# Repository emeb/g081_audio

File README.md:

# g081_audio

A Eurorack reverb module based on the STM32G081

## What it is

The G081 Audio module is an extremely simplified audio effects processor for Eurorack that's designed specifically to run the original MIDIVerb algorithms. Its audio conversion resolution is comparable to the original MIDIVerb and its processing power and memory capacity are just enough to handle the requirements of the algorithms. Essentially it is a proof-of-concept in minimalism.

## Background

In 2021 I was involved in a project to reverse-engineer the MIDIVerb which I've documented over here: [MIDIVerb_RE](https://github.com/emeb/MIDIVerb_RE). Once that effort was wrapped up I had some curiosity about how well those algorithms could be implemented on modern low-cost microprocessors so I did some tests that showed the initial emulation approach was too costly to run well on low-spec processors because there was considerable overhead in the the interpretation approach that was used. The alternative was to "compile" the algorithms into equivalent C code which could then be further optimized into fast machine code by high quality C compilers available today. This is the method used in the G081 Audio module.

## Hardware Features

The hardware of the module includes the following features:

- STM32G081KB Arm Cortex M0+ microcontroller
  - 64MHz
  - 128kB Flash
  - 36kB SRAM
  - 12-bit ADC with multipexed inputs
  - 2x 12-bit DACs
  - I2S, I2C and SPI ports
- PT8211 I2S stereo DAC
  - choice of on-chip DAC or I2S DAC for Euro-level audio outputs 
- Optional SPI flash chip (up to 32MB capacity)
- 12MHz crystal oscillator
- 64x32 I2C OLED display
- 2 CV inputs (+/-5V range with offset pots)
- Stereo audio inputs (12-bit resolution, +/-7V range)
- Stereo audio outputs (12- or 16-bit resolution, +/-7V range)
- 3.3V logic-level full-duplex serial port for diagnostics
- 6HP wide
- Standard 16-pin Euro power jack w/ shroud and reverse protection.

The main board has components on both sides - pots, jacks and OLED display on the front and all the remaining parts, including the Eurorack power jack on the back. The board has two "solder blob" type jumpers which allow selection of the output source - either the DACs internal to the STM32G081 or the PT8211 I2S DAC - the present firmware assumes the PT8211 is used. A footprint for an optional SPI flash chip is available although the present firmware does not require it.

## Firmware Features

The primary MIDIVerb software provides these features:

- 63 Original MIDIVerb algorithms selected by CV1
  - Smooth muting during program changes.
  - MIDIVerb algorithm number displayed on OLED.
  - Characteristics (duration, type) temporarily shown on display during changes.
- Wet/Dry mixing via CV2
  - Mix setting displayed on OLED.
- Input / Ouput level indicators
  - Low / normal / Clip level displayed as grayscale
- Compile-time option for OLED blanking.

## Design Collateral

This repository contains both Hardware and Firmware design info. Please refer to the README.md files withing the respective directories for further details.

[Hardware](./Hardware/README.md)

[Firmware](./Firmware/README.md)

## Build Notes

Since this project was first released there has been at least one alternate layout built by others in the community which unfortunately suffered from severe noise caused by the OLED which leaked into the audio path. The original layout provided here does not suffer from that problem so it's worthwhile noting that if you do choose to respin this design it would be wise to observe good layout principles:
- Maintain as contiguous a ground plane as is possible
- Think about the paths that supply and return currents are forced to take through your layout and how to keep the digital and analog paths separate.

In particular, the OLED is prone to generating strong current spikes when it is refreshing any active pixels and the PT8211 I2S DAC has very poor power supply rejection so when those two devices are present in the same design you must use care to keep them from fighting. I've provided a compile-time option to blank the OLED after a few seconds which can work around this issue but with good layout this should not be necessary.

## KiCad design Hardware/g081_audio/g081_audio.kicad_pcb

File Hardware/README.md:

# G081 Audio Hardware

This directory contains the KiCAD design files for the G081 Audio module, including both the passive front panel and the electrical rear panel.

A PDF schematic is available here: [G081 Audio Schematic](./g081_audio_schematic.pdf)

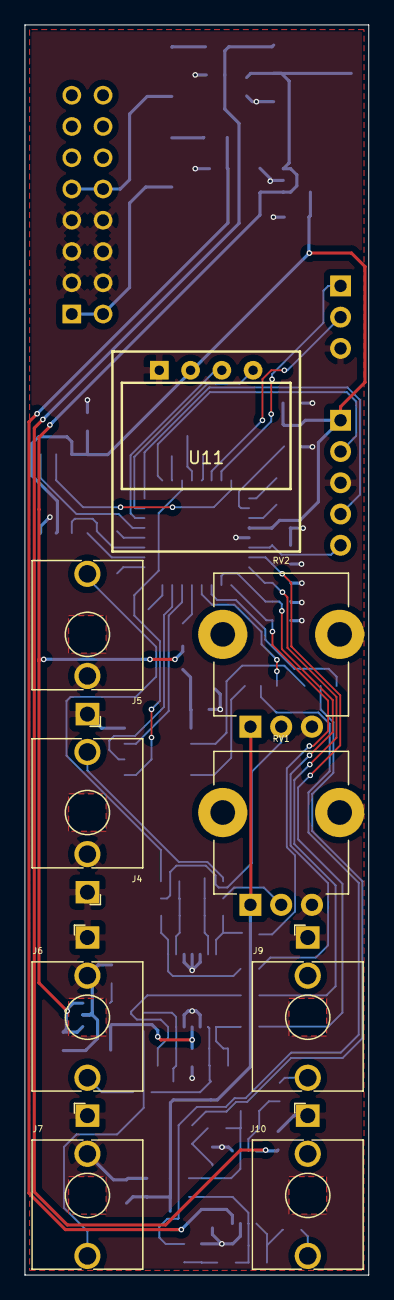
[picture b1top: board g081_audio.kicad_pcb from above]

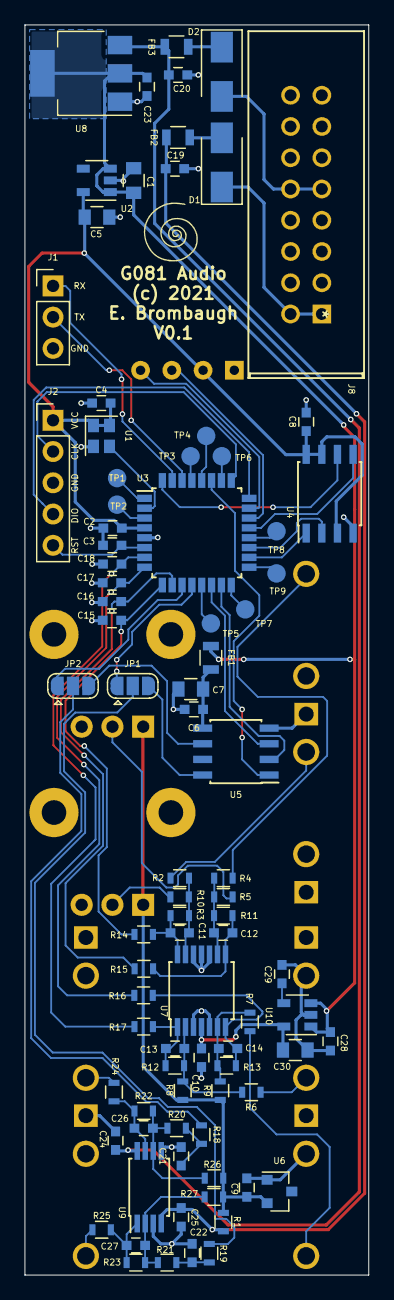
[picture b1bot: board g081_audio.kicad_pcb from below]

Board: 2 copper layers, 27.9 x 101.6 mm, 96 parts (87 on the bottom side), 69 nets.

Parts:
C1, C5, C7, C30: 10uf; C_0805
C2, C3, C4, C6, C8, C9, C10, C24, C25: 0.1uf; C_0603
C11, C12, C13, C14: 330pf; C_0603
C15, C16, C17, C18, C29: 0.01uf; C_0603
C19, C20, C23, C28: 1uf; C_0603
C21, C22: 4.7nf; C_0603
C26, C27: 75pf; C_0603
D1, D2: D; D_SMA
FB1, FB2, FB3: 220; R_0805
J1: Serial; Pin_Header_Straight_1x03_Pitch2.54mm
J2: SWD; Pin_Header_Straight_1x05_Pitch2.54mm
J4, J5, J6, J7, J9, J10: AudioJack2_SwitchT; Jack_3.5mm_QingPu_WQP-PJ398SM_Vertical_CircularHoles
J8: Conn_02x08_Odd_Even; 5103308-3
JP1, JP2: SolderJumper_3_Open; SolderJumper-3_P1.3mm_Open_RoundedPad1.0x1.5mm
R1: 1.5k; R_0603
R2, R4, R6, R7, R8, R9: 100k; R_0603
R3, R5: 49.9k; R_0603
R10, R11, R12, R13: 33k; R_0603
R14, R15, R16, R17, R24, R25: 100; R_0603
R18, R19: 1k; R_0603
R20, R21: 16k; R_0603
R22, R23, R26, R27: 71.5k; R_0603
RV1, RV2: 10k; Potentiometer_TT_P0915N
Ref**: Val**; avatar_small
TP1, TP2, TP3, TP4, TP5, TP6, TP7, TP8, TP9: TestPoint; Measurement_Point_Round-SMD-Pad_Small
U1: 12MHz; Oscillator_SMD_SeikoEpson_SG210-4pin_2.5x2.0mm
U2: MCP1802x-xx02xOT; SOT-23-5
U3: STM32G081KB; LQFP-32_7x7mm_Pitch0.8mm
U4: W25Q32JVSS; SOIC-8_208mil_Pitch1.27mm
U5: PT8211; SOIC-8_3.9x4.9mm_Pitch1.27mm
U6: LM4040DBZ-5; SOT-23
U7: MCP6004; TSSOP-14_4.4x5mm_Pitch0.65mm
U8: LM1117-5.0; SOT-223-3_TabPin2
U9: TL072PW; TSSOP-8_4.4x3mm_Pitch0.65mm
U10: LP2985-3.3; SOT-23-5
U11: OLED_I2C; OLED_I2C_64x32_0.95

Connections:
+3.3VA: C10.1, C30.1, U7.4, U10.5
+3V3: C2.1, C4.1, C5.1, C8.1, J2.1, U1.1, U1.4, U2.5, U3.4, U4.3, U4.7, U4.8, U11.2
+5V: C1.1, C23.1, C28.1, FB1.1, U2.1, U2.3, U8.2, U10.1, U10.3
+12V: C20.1, C24.1, FB3.1, U8.3, U9.8
-5VA: C9.1, R1.1, R8.1, R9.1, R26.2, R27.2, RV1.1, RV2.1, U6.2
-12V: C19.1, C25.2, FB2.1, R1.2, U9.4
/CLK12MHz: U1.3, U3.2
/DAC_L: JP2.3, U5.6
/DAC_R: JP1.3, U5.8
/I2C2_SCL: U3.22, U11.3
/I2C2_SDA: U3.23, U11.4
/I2S_CK: U3.27, U5.1
/I2S_SD: U3.14, U5.3
/I2S_WS: U3.15, U5.2
/MCU_L: JP2.1, U3.11
/MCU_R: JP1.1, U3.12
/NRST: C3.1, J2.5, U3.6
/SPI2_MISO: U3.19, U4.2
/SPI2_MOSI: U3.21, U4.5
/SPI2_NSS: U3.18, U4.1
/SPI2_SCK: U3.32, U4.6
/SWCLK: J2.2, U3.25
/SWDIO: J2.4, U3.24
/USART_RX: J1.1, U3.31
/USART_TX: J1.2, U3.30
/VDAC: C6.1, C7.1, FB1.2, U5.5
GND: C1.2, C2.2, C3.2, C4.2, C5.2, C6.2, C7.2, C8.2, C9.2, C10.2, C15.2, C16.2, C17.2, C18.2, C19.2, C20.2, C21.2, C22.2, C23.2, C24.2, C25.1, C28.2, C29.2, C30.2, J1.3, J2.3, J4.S, J4.TN, J5.S, J5.TN, J6.S, J6.TN, J7.S, J7.TN, J8.3, J8.4, J8.5, J8.6, J8.7, J8.8, J9.S, J10.S, RV1.3, RV2.3, U1.2, U2.2, U3.5, U4.4, U5.4, U6.1, U7.3, U7.5, U7.10, U7.11, U7.12, U8.1, U9.3, U9.5, U10.2, U11.1
unnamed: C11.1, R10.1, R14.2, U7.14
unnamed: C11.2, R2.1, R3.1, R10.2, U7.13
unnamed: C12.1, R11.1, R15.2, U7.8
unnamed: C12.2, R4.1, R5.1, R11.2, U7.9
unnamed: C13.1, R12.1, R17.2, U7.1
unnamed: C13.2, R6.1, R8.2, R12.2, U7.2
unnamed: C14.1, R13.1, R16.2, U7.7
unnamed: C14.2, R7.1, R9.2, R13.2, U7.6
unnamed: C21.1, R18.1, R20.2
unnamed: C22.1, R19.1, R21.2
unnamed: C26.1, R20.1, R22.2, R26.1, U9.6
unnamed: C26.2, R22.1, R24.2, U9.7
unnamed: C27.1, R21.1, R23.2, R27.1, U9.2
unnamed: C27.2, R23.1, R25.2, U9.1
unnamed: C29.1, U10.4
unnamed: D1.1, J8.1, J8.2
unnamed: D1.2, FB2.2
unnamed: D2.1, FB3.2
unnamed: D2.2, J8.9, J8.10
unnamed: J4.T, R2.2
unnamed: J5.T, R4.2
unnamed: J6.T, R6.2
unnamed: J7.T, R7.2
unnamed: J9.T, R24.1
unnamed: J10.T, R25.1
unnamed: R3.2, RV1.2
unnamed: R5.2, RV2.2
unnamed: TP1.1, U3.1
unnamed: TP2.1, U3.3
unnamed: TP3.1, U3.29
unnamed: TP4.1, U3.28
unnamed: TP5.1, U3.13
unnamed: TP6.1, U3.26
unnamed: TP7.1, U3.16
unnamed: TP8.1, U3.20
unnamed: TP9.1, U3.17
cv1: C15.1, R14.1, U3.9
cv2: C16.1, R15.1, U3.10
in_l: C18.1, R17.1, U3.7
in_r: C17.1, R16.1, U3.8
out_l: JP2.2, R18.2
out_r: JP1.2, R19.2

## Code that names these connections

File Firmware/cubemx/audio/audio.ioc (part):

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Mcu.Name=STM32G081KBTx
Mcu.Package=LQFP32
Mcu.UserName=STM32G081KBTx
PA0.Mode=IN0
PA0.Signal=ADC1_IN0
PA1.Mode=IN1
PA1.Signal=ADC1_IN1
PA10.Mode=Full_Duplex_Master
PA10.Signal=SPI2_MOSI
PA11\ [PA9].Mode=I2C
PA11\ [PA9].Signal=I2C2_SCL
PA12\ [PA10].Mode=I2C
PA12\ [PA10].Signal=I2C2_SDA
PA13.Mode=Serial_Wire
PA13.Signal=SYS_SWDIO
PA14-BOOT0.Mode=Serial_Wire
PA14-BOOT0.Signal=SYS_SWCLK
PA2.Mode=IN2
PA2.Signal=ADC1_IN2
PA3.Mode=IN3
PA3.Signal=ADC1_IN3
PA4.Signal=COMP_DAC11_group
PA5.Signal=COMP_DAC12_group
PA7.Mode=Half_Duplex_Master
PA7.Signal=I2S1_SD
PA8.Mode=NSS_Signal_Hard_Output
PA8.Signal=SPI2_NSS
PA9.Mode=Full_Duplex_Master
PA9.Signal=SPI2_MISO
PB0.Mode=Half_Duplex_Master
PB0.Signal=I2S1_WS
PB1.Mode=PWM Generation3 CH3N
PB1.Signal=TIM1_CH3N
PB3.Mode=Half_Duplex_Master
PB3.Signal=I2S1_CK
PB6.Mode=Asynchronous
PB6.Signal=USART1_TX
PB7.Mode=Asynchronous
PB7.Signal=USART1_RX
PB8.Mode=Full_Duplex_Master
PB8.Signal=SPI2_SCK
PC14-OSC32_IN\ (PC14).Mode=HSE-External-Clock-Source
PC14-OSC32_IN\ (PC14).Signal=RCC_OSC_IN
RCC.HSE_VALUE=12000000
RCC.SYSCLKFreq_VALUE=64000000
RCC.SYSCLKSource=RCC_SYSCLKSOURCE_PLLCLK
board=custom

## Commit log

2025-07-13 Initial checkin
2025-07-14 Added schematic and more documentation.
2025-07-14 Schematic updates - printing prefs, text notes, input gain, BOM.
2025-07-14 minor text tweak
2025-08-20 fix issue found with newer compilers
2025-08-22 Added optional OLED blanking
2025-08-23 Update README with layout notes.

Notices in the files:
Hardware/g081_audio/g081_audio.kicad_pcb:
(c) 2021
parts and their libraries:
Copyright 2016 Accelerated Designs. All rights reserved.
